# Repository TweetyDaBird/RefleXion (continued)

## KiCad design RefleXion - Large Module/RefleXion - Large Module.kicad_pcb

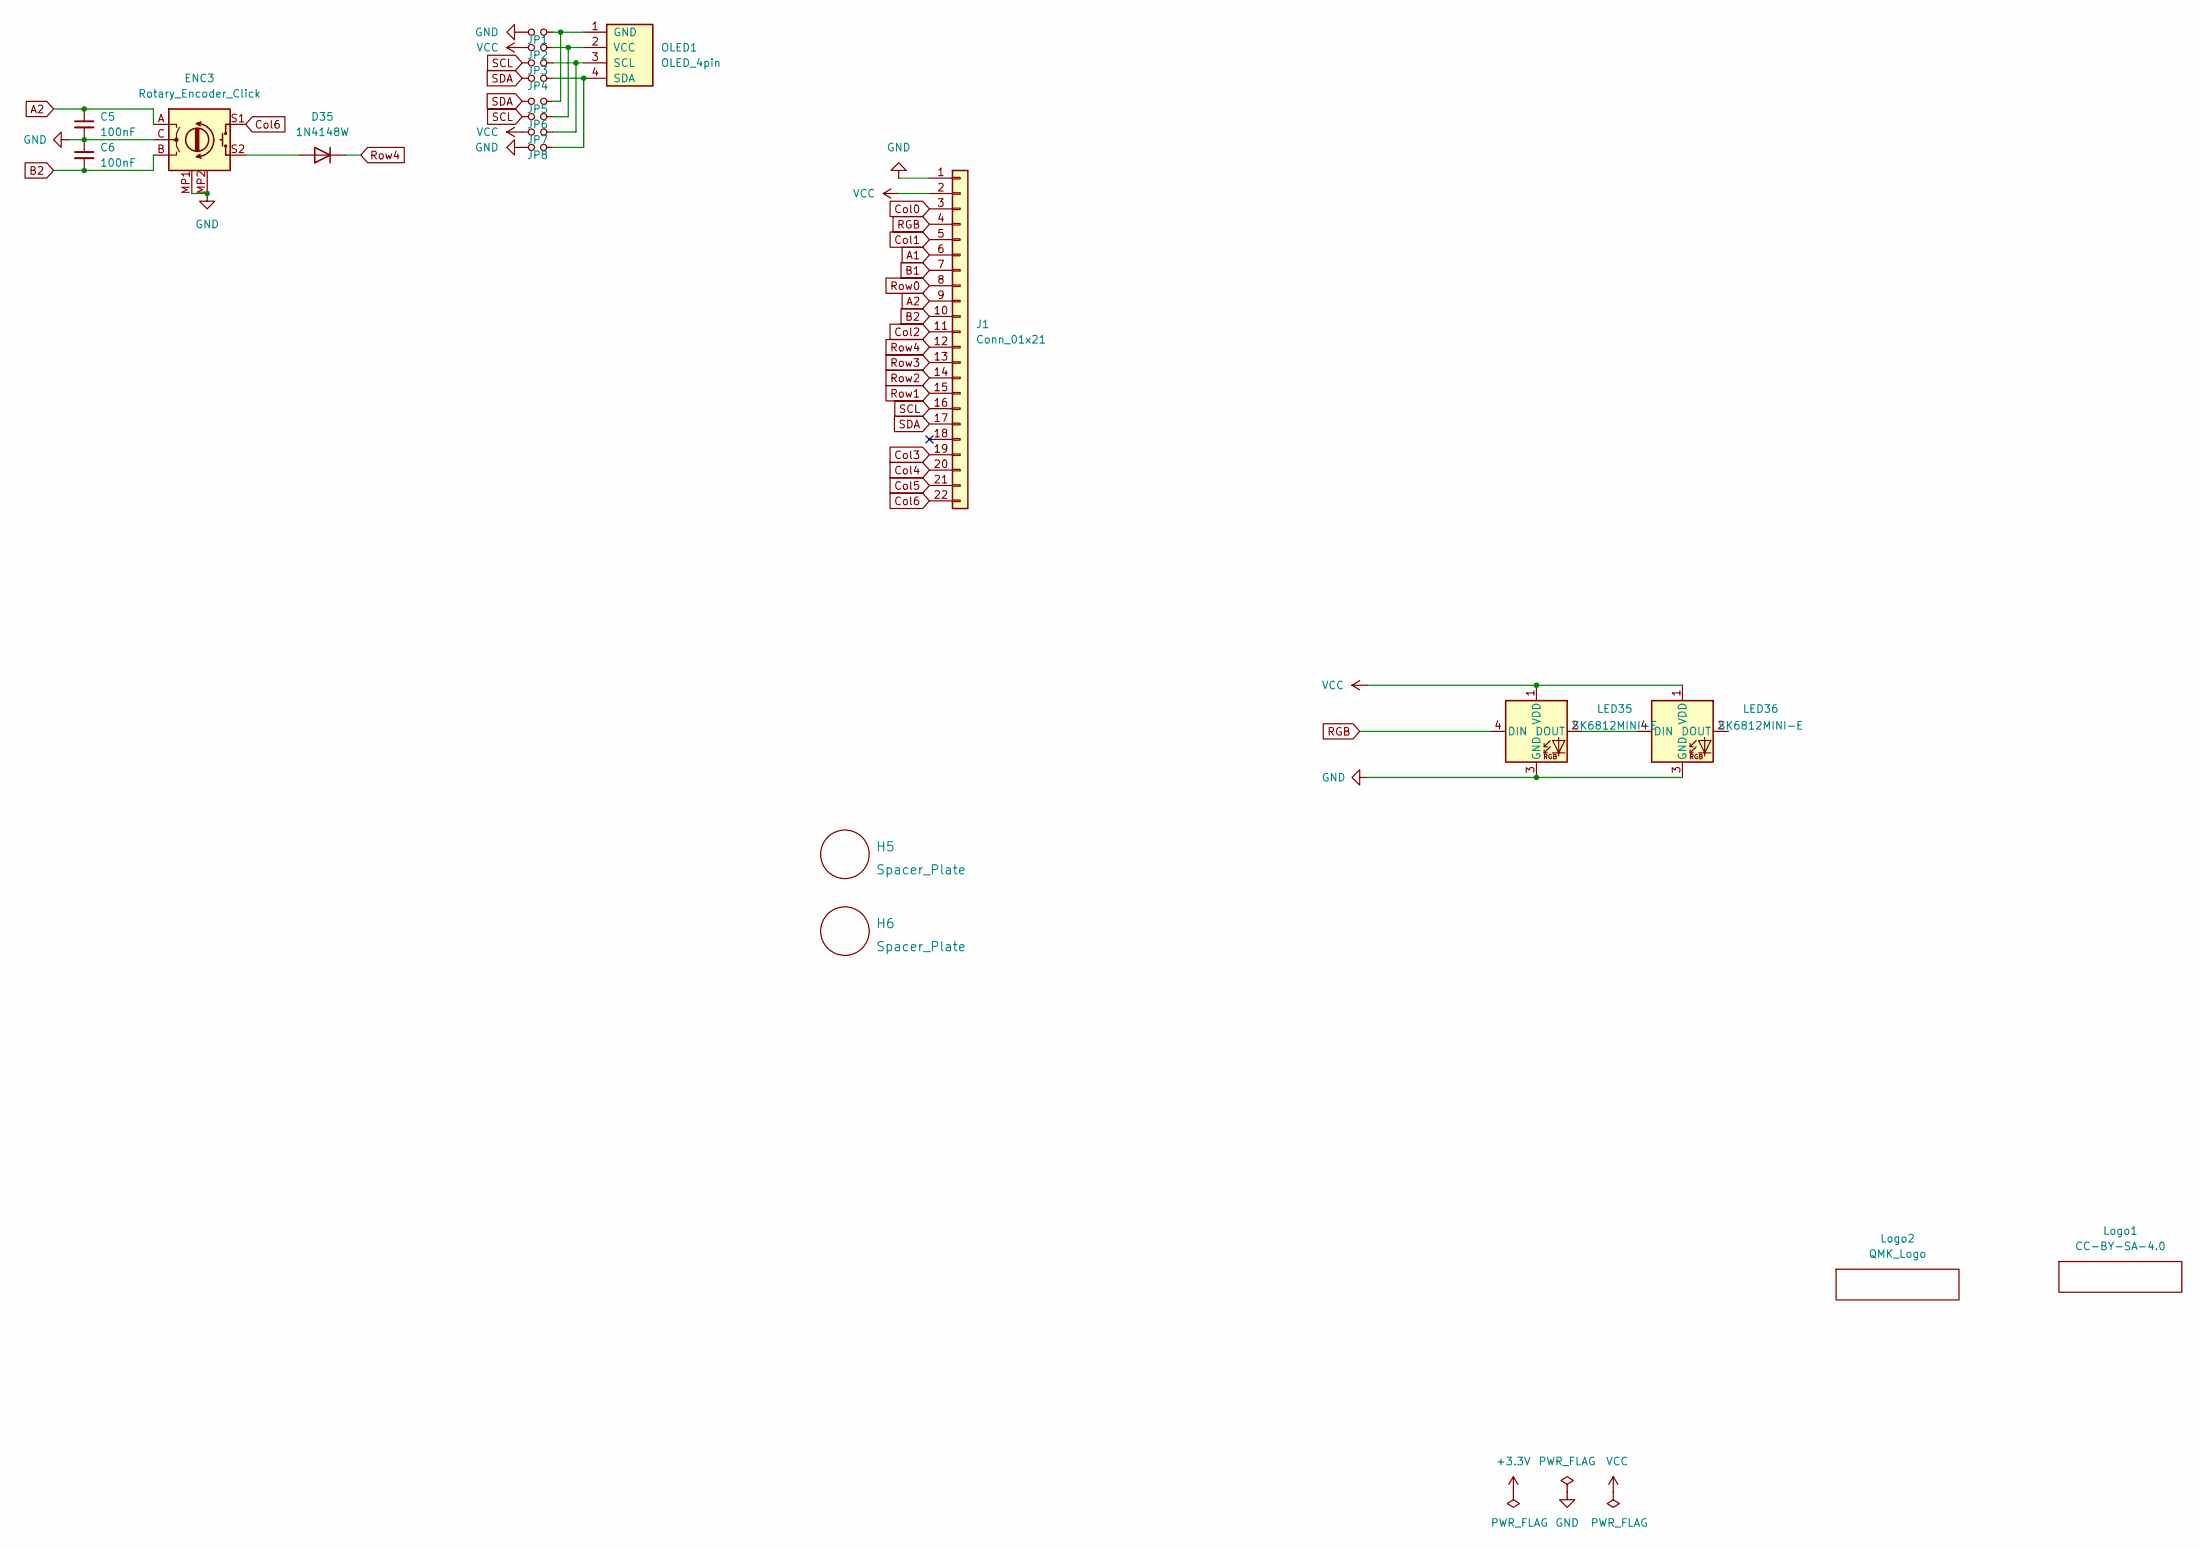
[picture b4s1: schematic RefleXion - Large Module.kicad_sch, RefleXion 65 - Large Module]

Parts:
C5, C6: 100nF; C_0603_1608Metric_Pad1.08x0.95mm_HandSolder
D35: 1N4148W; D_SOD-123
ENC3: Rotary_Encoder_Click; Encoder_Alps_EC11E_Small
H5, H6: Spacer_Plate; Spacer Plate hole
J1: Conn_01x21; PinHeader_1x22_P2.54mm_Vertical
JP1, JP2, JP3, JP4, JP5, JP6, JP7, JP8: Jumper_NO_Small; Jumper_Mini
LED35, LED36: SK6812MINI-E; MX_SK6812MINI-E_REVERSIBLE
Logo1: CC-BY-SA-4.0; CC_BY_SA_40
Logo2: QMK_Logo; Powered_by_QMK
OLED1: OLED_4pin; SSD1306-0.91-OLED-4pin-128x32

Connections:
A1: J1.6
A2: C5.1, ENC3.A, J1.9
B1: J1.7
B2: C6.2, ENC3.B, J1.10
Col0: J1.3
Col1: J1.5
Col2: J1.11
Col3: J1.19
Col4: J1.20
Col5: J1.21
Col6: ENC3.S1, J1.22
GND: C5.2, C6.1, ENC3.C, ENC3.MP1 (GND), ENC3.MP2 (GND), J1.1, JP1.2, JP8.2, LED35.3 (GND), LED36.3 (GND)
unnamed: D35.2 (A), ENC3.S2
unnamed: JP1.1, JP5.1, OLED1.1 (GND)
unnamed: JP2.1, JP6.1, OLED1.2 (VCC)
unnamed: JP3.1, JP7.1, OLED1.3 (SCL)
unnamed: JP4.1, JP8.1, OLED1.4 (SDA)
unnamed: LED35.2 (DOUT), LED36.4 (DIN)
RGB: J1.4, LED35.4 (DIN)
Row0: J1.8
Row1: J1.15
Row2: J1.14
Row3: J1.13
Row4: D35.1 (K), J1.12
SCL: J1.16, JP3.2, JP6.2
SDA: J1.17, JP4.2, JP5.2
VCC: J1.2, JP2.2, JP7.2, LED35.1 (VDD), LED36.1 (VDD)

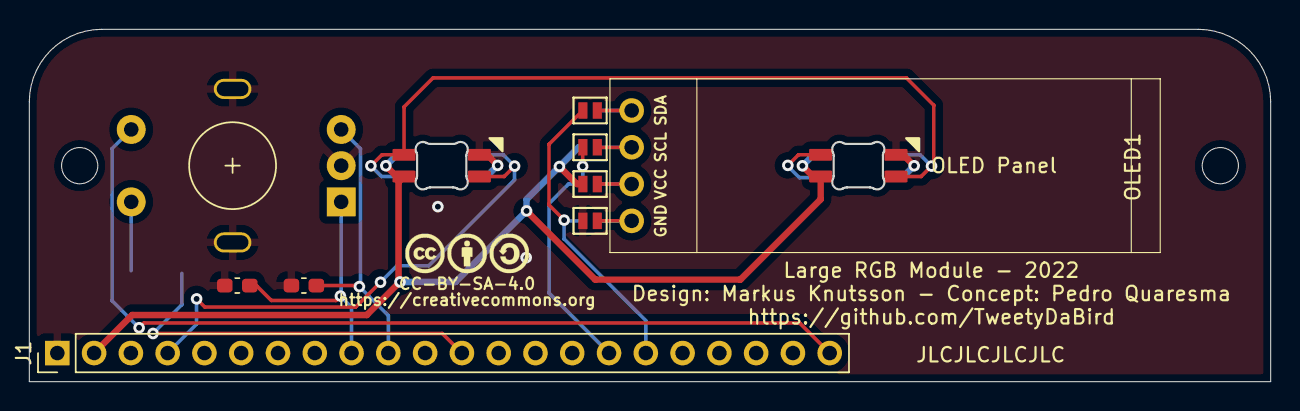
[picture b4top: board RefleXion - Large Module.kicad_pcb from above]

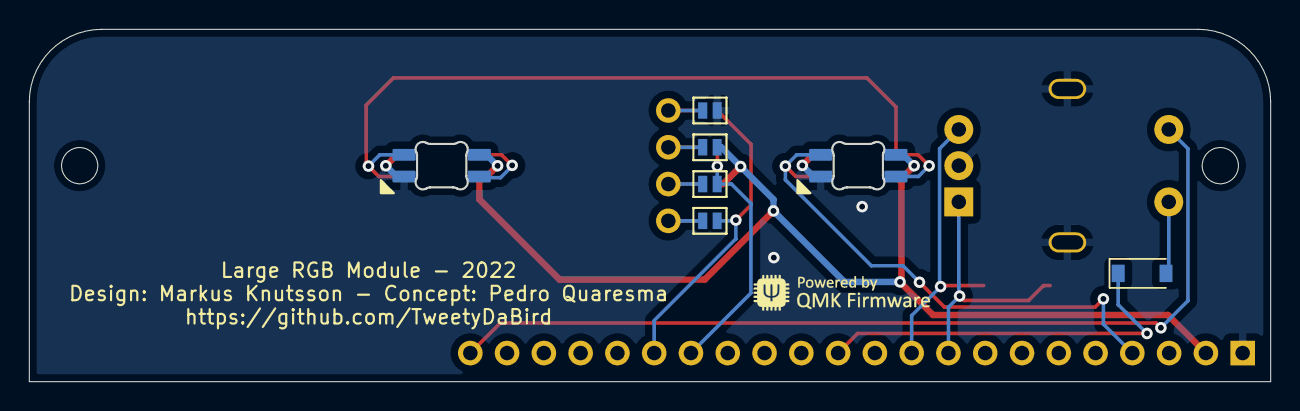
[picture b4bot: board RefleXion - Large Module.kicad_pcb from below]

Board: 2 copper layers, 85.7 x 24.3 mm, 20 parts (6 on the bottom side), 15 nets.

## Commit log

2022-10-27 Adding Reflexion 60
2022-11-29 fixes to RGB
2022-11-29 updated for RGB
2024-01-26 big dump
2024-01-31 new layout
2024-01-31 working route
2024-02-09 X65 initial commit
2024-02-09 Cleanup of old files
2024-02-09 X65 v1.10 final tweaks
2024-02-09 Renaming/Moving files
2024-04-04 v1.10 test1
2024-04-04 Test Mosfet version
2024-04-05 Reflexion X65 v1.10
    PCB finalized
2024-04-19 Reflexion X65 v1.10
    Prototype
2024-05-09 Ignore production
2025-06-26 Updated gitignore
2025-06-26 x65 Rear Plate
2025-06-26 x65 - Plate OLED
2025-06-26 x65 - Plate Full
2025-06-26 x65 - Front Plate ENC
2025-06-26 x65 - Front Plate Blank
2025-06-26 x65 v1.2 incomplete
2025-06-26 gitignore
2025-07-20 in progress grid
